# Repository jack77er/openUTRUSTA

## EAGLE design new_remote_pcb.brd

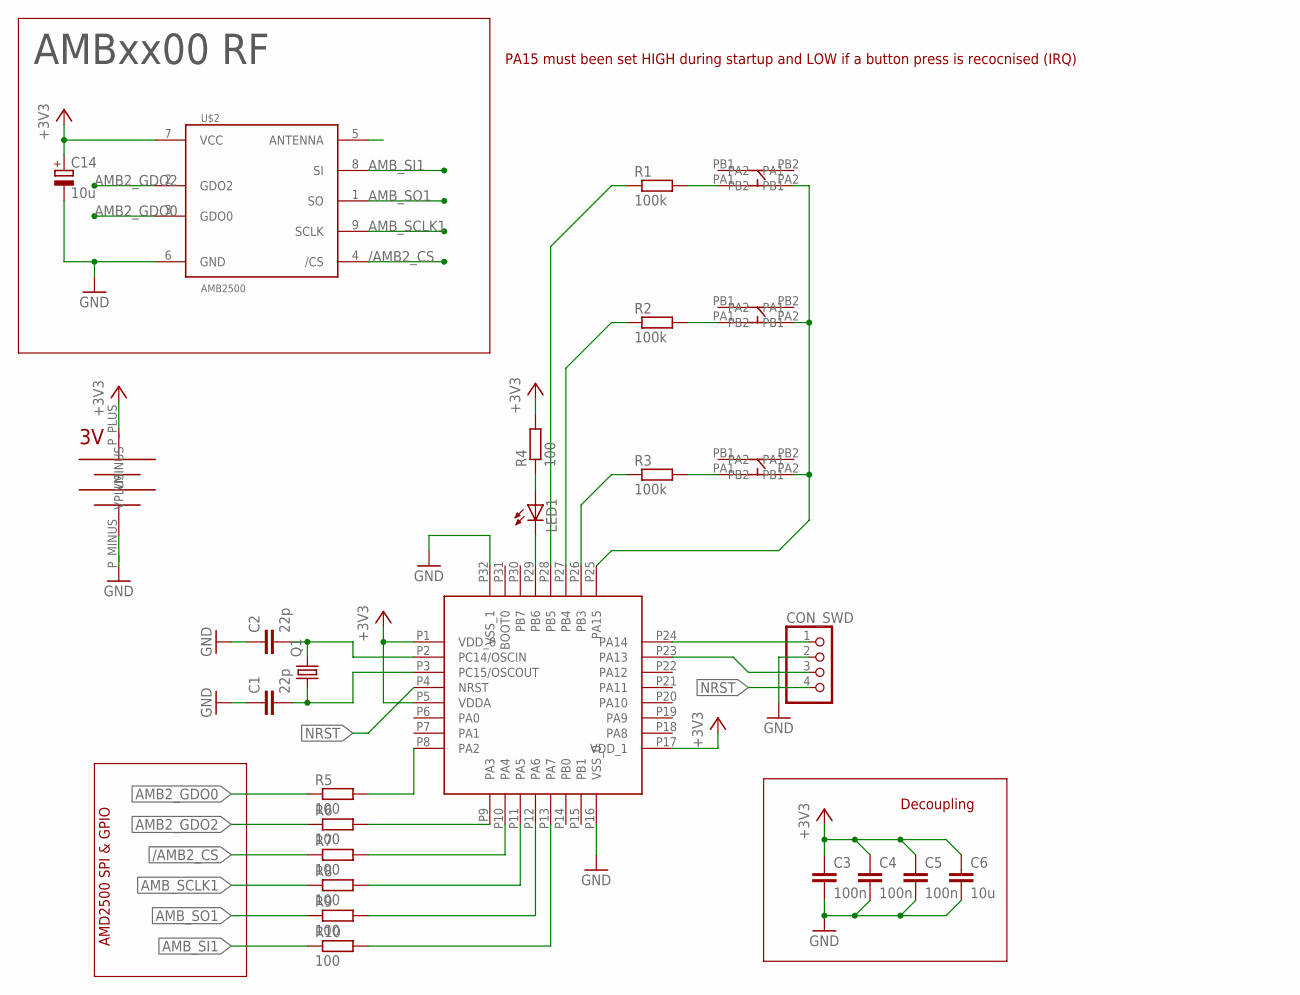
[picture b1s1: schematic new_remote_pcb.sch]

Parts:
C1, C2: 22p; C0805K
C3, C4, C5: 100n; C0805
C6: 10u; C0805
C14: 10u; A/3216-18W
CON_SWD: PINHD-1X4; 1X04
LED1: LED_E; LED_1206
Q1: CRYSTALHC49UP; HC49UP
R1, R2, R3: 100k; R0805W
R4: 100; R0805W
R5, R6, R7, R8, R9, R10: 100; R0805
U$1: STM32L051K8T6; LQFP32
U$2: AMB2500; AMB8400
U$3: KEYSTONE_2462; 2462
U$4, U$5, U$6: C&K_KSC_BUTTONS; C&K_KSC9

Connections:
+3V3: C3.1, C4.1, C5.1, C6.1, C14.+, R4.2, U$1.P1 (VDD_0), U$1.P5 (VDDA), U$1.P17 (VDD_1), U$2.7 (VCC), U$3.P_PLUS (VPLUS)
/AMB2_CS: R7.1, U$2.4 (/CS)
/AMB2_CS_UC: R7.2, U$1.P10 (PA4)
AMB2_GDO0: R5.1, U$2.3 (GDO0)
AMB2_GDO0_UC: R5.2, U$1.P8 (PA2)
AMB2_GDO2: R6.1, U$2.2 (GDO2)
AMB2_GDO2_UC: R6.2, U$1.P9 (PA3)
AMB_SCLK1: R8.1, U$2.9 (SCLK)
AMB_SCLK1_UC: R8.2, U$1.P11 (PA5)
AMB_SI1: R10.1, U$2.8 (SI)
AMB_SI1_UC: R10.2, U$1.P13 (PA7)
AMB_SO1: R9.1, U$2.1 (SO)
AMB_SO1_UC: R9.2, U$1.P12 (PA6)
GND: C1.1, C2.1, C3.2, C4.2, C5.2, C6.2, C14.-, CON_SWD.2, U$1.P16 (VSS_0), U$1.P32 (VSS_1), U$2.6 (GND), U$3.P_MINUS (VMINUS)
unnamed: U$1.P25 (PA15), U$4.PA2 (PB2), U$5.PA2 (PB2), U$6.PA2 (PB2)
unnamed: R1.2, U$4.PA1 (PB1)
unnamed: R2.2, U$5.PA1 (PB1)
unnamed: R3.2, U$6.PA1 (PB1)
unnamed: R3.1, U$1.P26 (PB3)
unnamed: R2.1, U$1.P27 (PB4)
unnamed: R1.1, U$1.P28 (PB5)
unnamed: LED1.A, R4.1
unnamed: LED1.C, U$1.P29 (PB6)
unnamed: C1.2, Q1.1, U$1.P3 (PC15/OSCOUT)
unnamed: C2.2, Q1.2, U$1.P2 (PC14/OSCIN)
unnamed: CON_SWD.1, U$1.P24 (PA14)
unnamed: CON_SWD.3, U$1.P23 (PA13)
NRST: CON_SWD.4, U$1.P4 (NRST)

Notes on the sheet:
AMBxx00 RF
AMD2500 SPI & GPIO
PA15 must been set HIGH during startup and LOW if a button press is recocnised (IRQ)
Decoupling

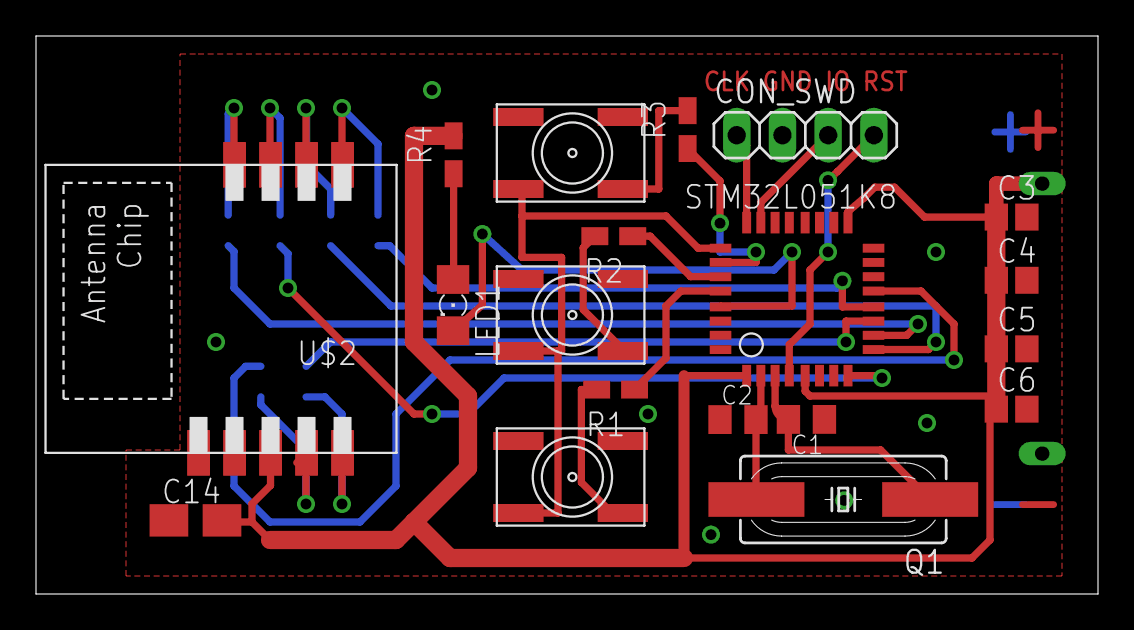
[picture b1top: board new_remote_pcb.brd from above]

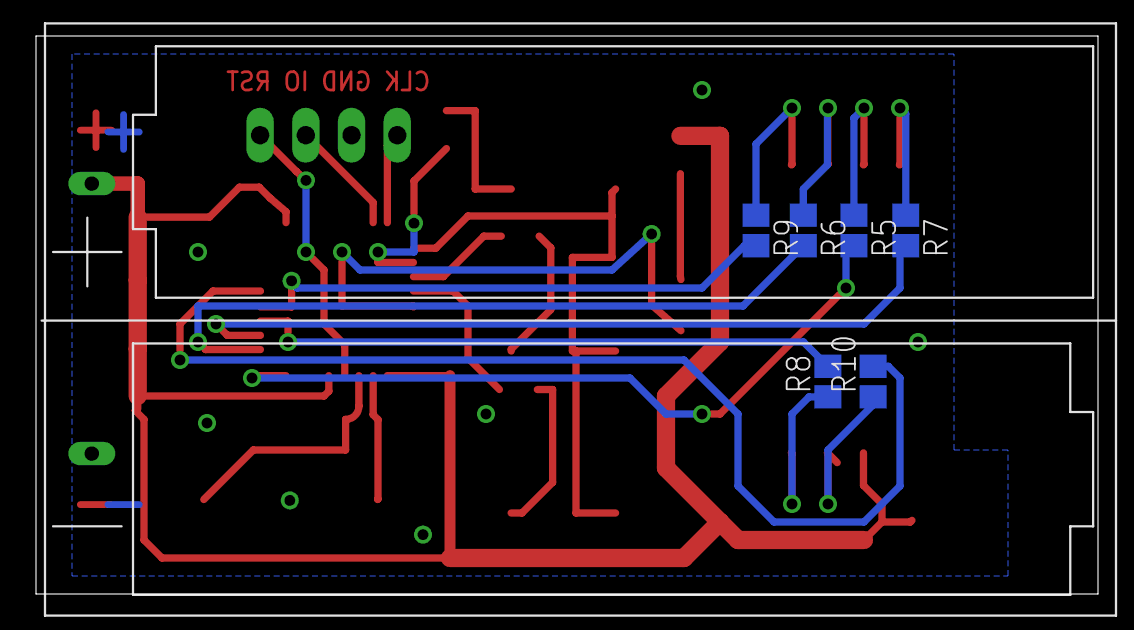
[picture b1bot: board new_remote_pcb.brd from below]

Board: 2 copper layers, 59.0 x 31.0 mm, 26 parts (7 on the bottom side), 28 nets.

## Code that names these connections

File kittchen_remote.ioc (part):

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Mcu.Name=STM32F030K6Tx
Mcu.Package=LQFP32
Mcu.UserName=STM32F030K6Tx
PA13.Mode=Serial-WireDebug
PA13.Signal=SYS_SWDIO
PA14.Mode=Serial-WireDebug
PA14.Signal=SYS_SWCLK
PA15.Signal=GPIO_Output
PA2.Signal=GPXTI2
PA3.Signal=GPIO_Input
PA4.Mode=NSS_Signal_Hard
PA4.Signal=SPI1_NSS
PA5.Mode=Full_Duplex_Master
PA5.Signal=SPI1_SCK
PA6.Mode=Full_Duplex_Master
PA6.Signal=SPI1_MISO
PA7.Mode=Full_Duplex_Master
PA7.Signal=SPI1_MOSI
PB3.Signal=GPXTI3
PB4.Signal=GPXTI4
PB5.Signal=GPXTI5
PB6.Signal=GPIO_Analog
PF0-OSC_IN.Mode=HSE-External-Oscillator
PF0-OSC_IN.Signal=RCC_OSC_IN
PF1-OSC_OUT.Mode=HSE-External-Oscillator
PF1-OSC_OUT.Signal=RCC_OSC_OUT
RCC.HSE_VALUE=16000000
RCC.SYSCLKSource=RCC_SYSCLKSOURCE_PLLCLK
